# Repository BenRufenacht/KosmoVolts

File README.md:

# KosmoVolts
 Music Thing Modular Volts expander converted to Kosmo format

[Schematic](https://github.com/TomWhitwell/Volts/blob/master/Collateral/Volts_Schematic.pdf)

Status:   
June 2022 - Boards have not been manufactured or tested

License:  
[CC-BY-SA](https://creativecommons.org/licenses/by-sa/3.0/)

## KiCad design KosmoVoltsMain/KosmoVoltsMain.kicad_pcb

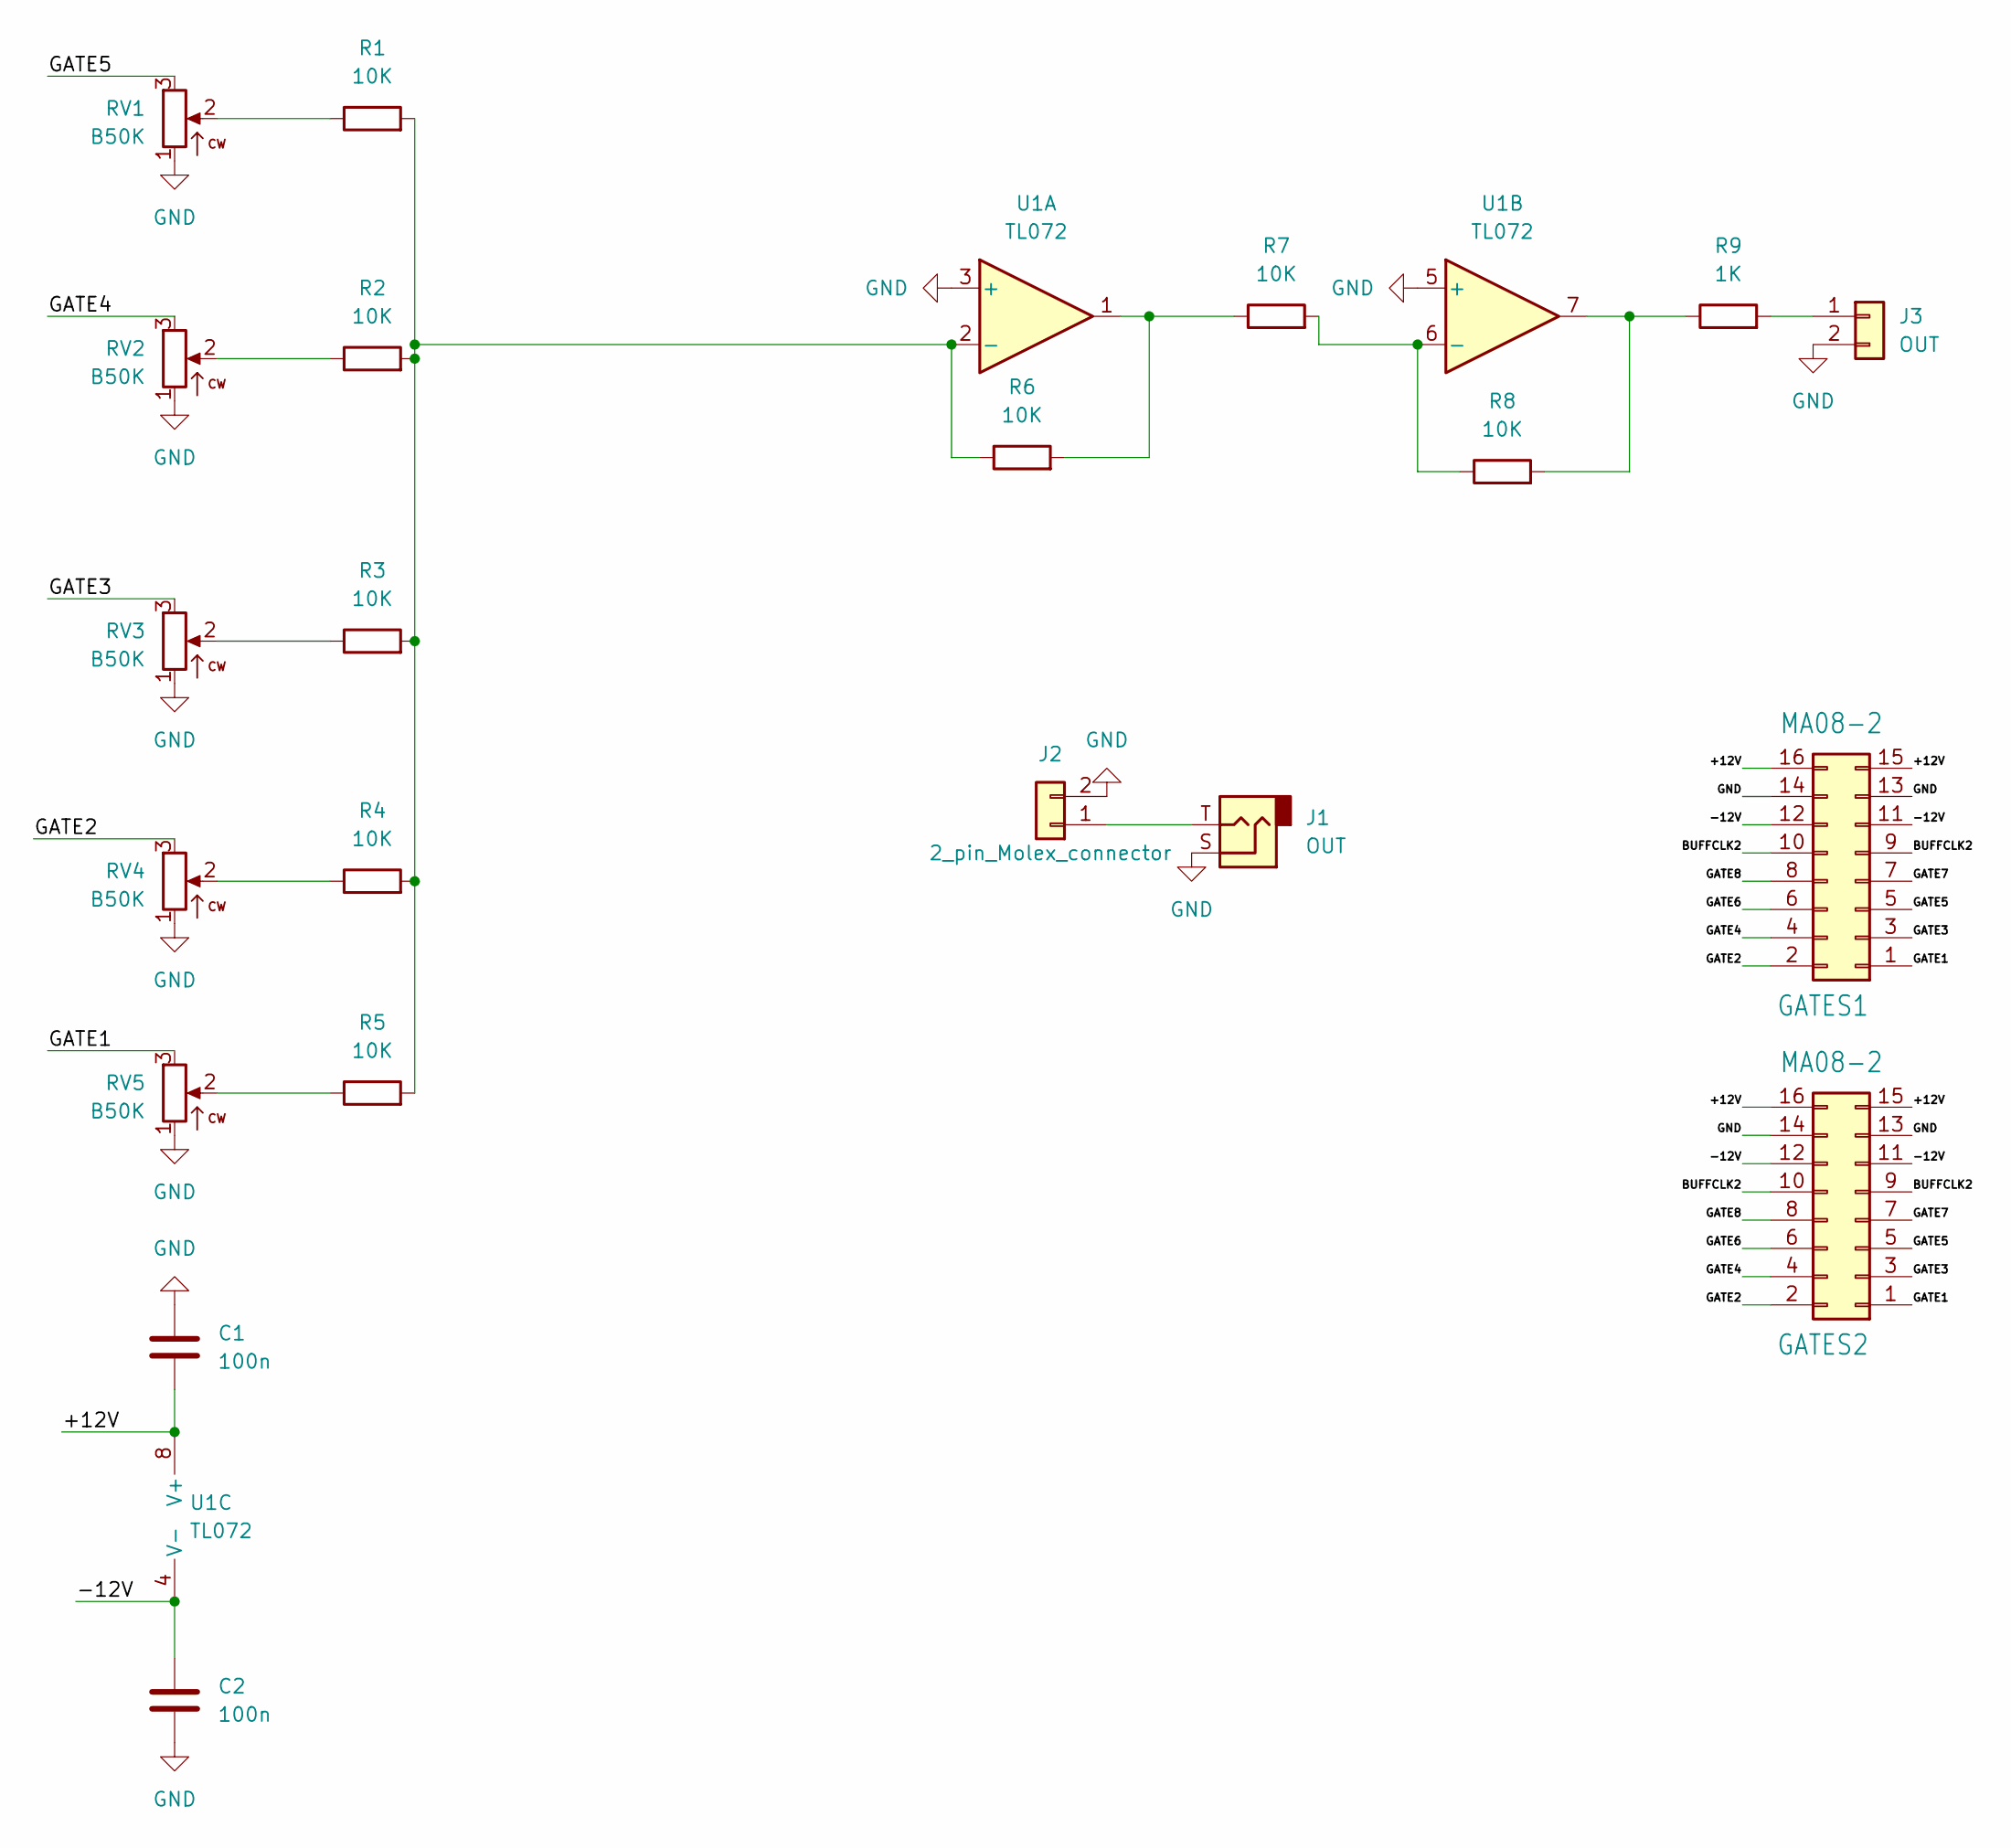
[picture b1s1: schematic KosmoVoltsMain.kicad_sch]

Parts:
C1, C2: 100n; C_Rect_L7.2mm_W2.5mm_P5.00mm_FKS2_FKP2_MKS2_MKP2
GATES1, GATES2: MA08-2; IDC-Header_2x08_P2.54mm_Vertical
J1: OUT; Jack_6.35mm_PJ_629HAN
J2: 2_pin_Molex_connector
J3: OUT; Molex_KK-254_AE-6410-02A_1x02_P2.54mm_Vertical
R1, R2, R3, R4, R5, R6, R7, R8: 10K; R_Axial_DIN0207_L6.3mm_D2.5mm_P10.16mm_Horizontal
R9: 1K; R_Axial_DIN0207_L6.3mm_D2.5mm_P10.16mm_Horizontal
RV1, RV2, RV3, RV4, RV5: B50K; Potentiometer_Alpha_RD901F-40-00D_Single_Vertical_centered
U1: TL072; DIP-8_W7.62mm_Socket_LongPads

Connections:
/+12V: C1.2, GATES1.15, GATES1.16, GATES2.15, GATES2.16, U1.8 (V+)
/-12V: C2.1, GATES1.11, GATES1.12, GATES2.11, GATES2.12, U1.4 (V-)
/BUFFCLK2: GATES1.9, GATES1.10, GATES2.9, GATES2.10
/GATE1: GATES1.1, GATES2.1, RV5.3
/GATE2: GATES1.2, GATES2.2, RV4.3
/GATE3: GATES1.3, GATES2.3, RV3.3
/GATE4: GATES1.4, GATES2.4, RV2.3
/GATE5: GATES1.5, GATES2.5, RV1.3
/GATE6: GATES1.6, GATES2.6
/GATE7: GATES1.7, GATES2.7
/GATE8: GATES1.8, GATES2.8
GND: C1.1, C2.2, GATES1.13, GATES1.14, GATES2.13, GATES2.14, J1.S, J2.2, J3.2, RV1.1, RV2.1, RV3.1, RV4.1, RV5.1, U1.3 (+), U1.5 (+)
unnamed: J1.T, J2.1
unnamed: J3.1, R9.2
unnamed: R1.1, RV1.2
unnamed: R1.2, R2.2, R3.2, R4.2, R5.2, R6.1, U1.2 (-)
unnamed: R2.1, RV2.2
unnamed: R3.1, RV3.2
unnamed: R4.1, RV4.2
unnamed: R5.1, RV5.2
unnamed: R6.2, R7.1, U1.1
unnamed: R7.2, R8.1, U1.6 (-)
unnamed: R8.2, R9.1, U1.7

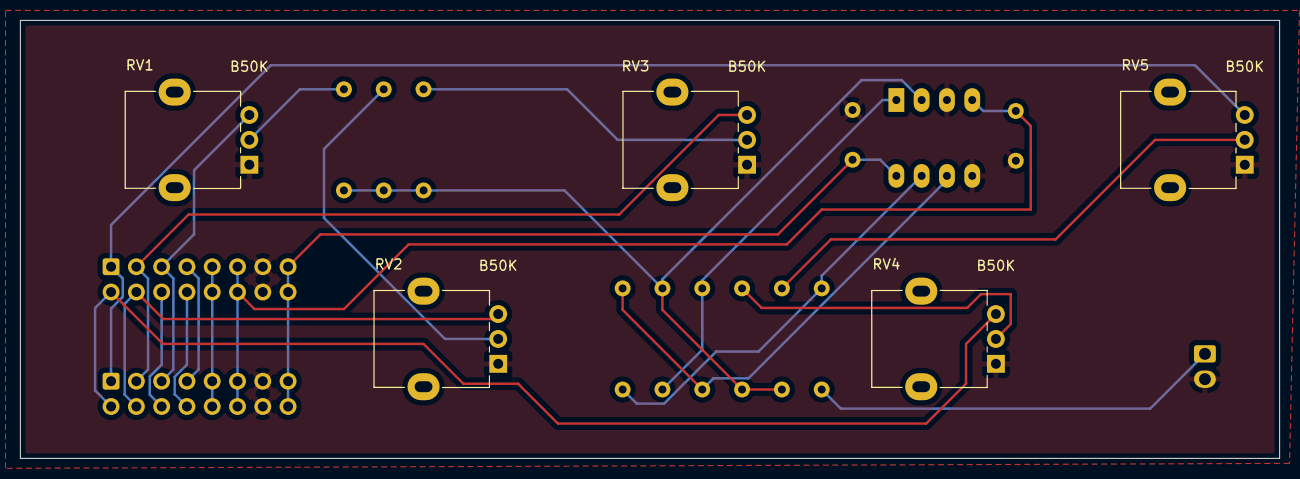
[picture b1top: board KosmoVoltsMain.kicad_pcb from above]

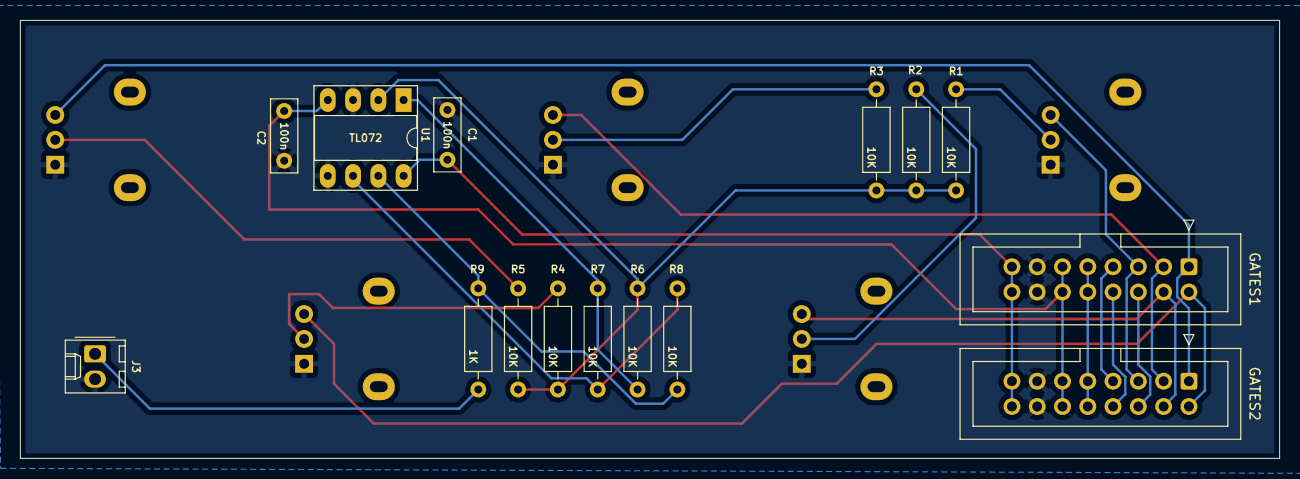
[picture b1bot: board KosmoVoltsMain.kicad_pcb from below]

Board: 2 copper layers, 126.5 x 44.0 mm, 20 parts (15 on the bottom side), 22 nets.

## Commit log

2022-06-09 Updated Panel Layout and Graphics
2022-06-10 Manufacturing Update
2022-07-31 Minor Silkscreen Update
